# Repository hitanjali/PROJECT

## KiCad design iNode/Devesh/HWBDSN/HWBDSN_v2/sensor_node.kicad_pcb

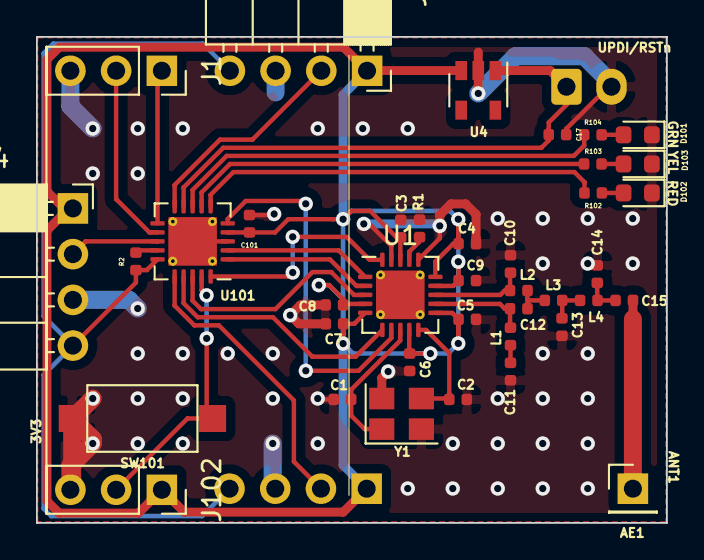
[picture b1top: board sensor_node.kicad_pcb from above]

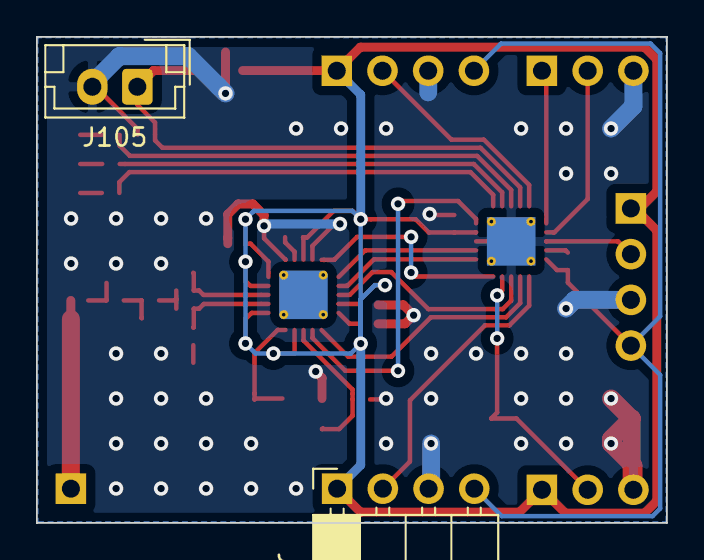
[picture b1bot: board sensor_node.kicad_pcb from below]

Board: 2 copper layers, 35.0 x 27.0 mm, 41 parts (2 on the bottom side), 33 nets.

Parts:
AE1: Antenna; PinHeader_1x01_P2.54mm_Vertical
C1: 12pF; C_0402_1005Metric
C2: 15pF; C_0402_1005Metric
C3, C4, C5, C6, C7, C8, C9: 0.1uF; C_0402_1005Metric
C10, C12: 3.9pF; C_0402_1005Metric
C11, C15: 220pF; C_0402_1005Metric
C13: 8.2pF; C_0402_1005Metric
C14: 5.6pF; C_0402_1005Metric
C17, C101: 0.1uF, 10V; C_0402_1005Metric
D101: RED; LED_0603_1608Metric
D102: YELLOW; LED_0603_1608Metric
D103: GREEN; LED_0603_1608Metric
J1: Conn_01x03_[UART]; PinSocket_1x03_P2.54mm_Vertical
J2: Conn_01x03_[PIR_1]; PinSocket_1x04_P2.54mm_Horizontal
J3: Conn_01x03_[PIR_2]; PinSocket_1x04_P2.54mm_Horizontal
J4: Conn_01x03_[PIR_3]; PinSocket_1x04_P2.54mm_Horizontal
J102: Conn_01x03_[UPDI]; PinSocket_1x03_P2.54mm_Vertical
J105: extenal_battery; JST_EH_B2B-EH-A_1x02_P2.50mm_Vertical
L1, L2, L4: 27nH; L_0402_1005Metric
L3: 22nH; L_0402_1005Metric
R1: 56K; R_0402_1005Metric
R2: 20k; R_0402_1005Metric
R102, R103, R104: 2.2K; R_0402_1005Metric
SW101: SW_Push; SW_SPST_CK_RS282G05A3
U1: CC110L; QFN-20-1EP_4x4mm_P0.5mm_EP2.7x2.7mm_ThermalVias
U4: AP7351D-30WS-7; SOT-23-5
U101: ATtiny1606-M; QFN-20-1EP_4x4mm_P0.5mm_EP2.7x2.7mm_ThermalVias
Y1: 26MHz Crystal, 10pF; Crystal_SMD_3225-4Pin_3.2x2.5mm

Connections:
+3V3: C3.1, C4.1, C5.1, C6.1, C7.1, C8.1, C9.1, C101.1, J2.1, J3.1, J4.1, J102.1, U1.4, U1.5, U1.9, U1.11, U1.14, U1.15, U1.18, U4.3, U101.4
/Sheet5FFE69EF/LDR: J2.4, J3.4, J4.4, R2.1, U101.15
/Sheet5FFE69EF/PIR_1: J2.2, U101.10
/Sheet5FFE69EF/PIR_2: J3.2, U101.16
/Sheet5FFE69EF/PIR_3: J4.2, U101.13
/Sheet5FFE69EF/to_LDR: R2.2, U101.14
/Sheet6001F810/GDO0: U1.6, U101.17
/Sheet6001F810/GDO2: U1.3, U101.18
/Sheet6001F810/GREEN: R104.1, U101.8
/Sheet6001F810/MISO: U1.2, U101.1
/Sheet6001F810/MOSI: U1.20, U101.20
/Sheet6001F810/PWR_MONITOR: C17.1, J105.1, U4.1, U101.9
/Sheet6001F810/RED: R102.1, U101.6
/Sheet6001F810/RESETn_UPDI: J102.2, SW101.1, U101.19
/Sheet6001F810/RXD: J1.1, U101.11
/Sheet6001F810/SCK: U1.1, U101.2
/Sheet6001F810/TXD: J1.2, U101.12
/Sheet6001F810/YELLOW: R103.1, U101.7
/Sheet6001F837/CSn: U1.7, U101.5
/Sheet6001F837/Q1: C1.1, U1.8, Y1.1
/Sheet6001F837/Q2: C2.1, U1.10, Y1.3
/Sheet6001F837/RFN: C10.2, L2.1, U1.13
/Sheet6001F837/RFP: C12.2, L1.2, U1.12
GND: C1.2, C2.2, C3.2, C4.2, C5.2, C6.2, C7.2, C8.2, C9.2, C10.1, C11.2, C13.2, C14.1, C17.2, C101.2, D101.1, D102.1, D103.1, J1.3, J2.3, J3.3, J4.3, J102.3, J105.2, R1.1, SW101.2, U1.16, U1.19, U4.2, U101.3, U101.21, Y1.2, Y1.4
unnamed: AE1.1, C15.2
unnamed: C11.1, L1.1
unnamed: C12.1, L2.2, L3.2
unnamed: C13.1, L3.1, L4.2
unnamed: C14.2, C15.1, L4.1
unnamed: D101.2, R102.2
unnamed: D102.2, R103.2
unnamed: D103.2, R104.2
unnamed: R1.2, U1.17

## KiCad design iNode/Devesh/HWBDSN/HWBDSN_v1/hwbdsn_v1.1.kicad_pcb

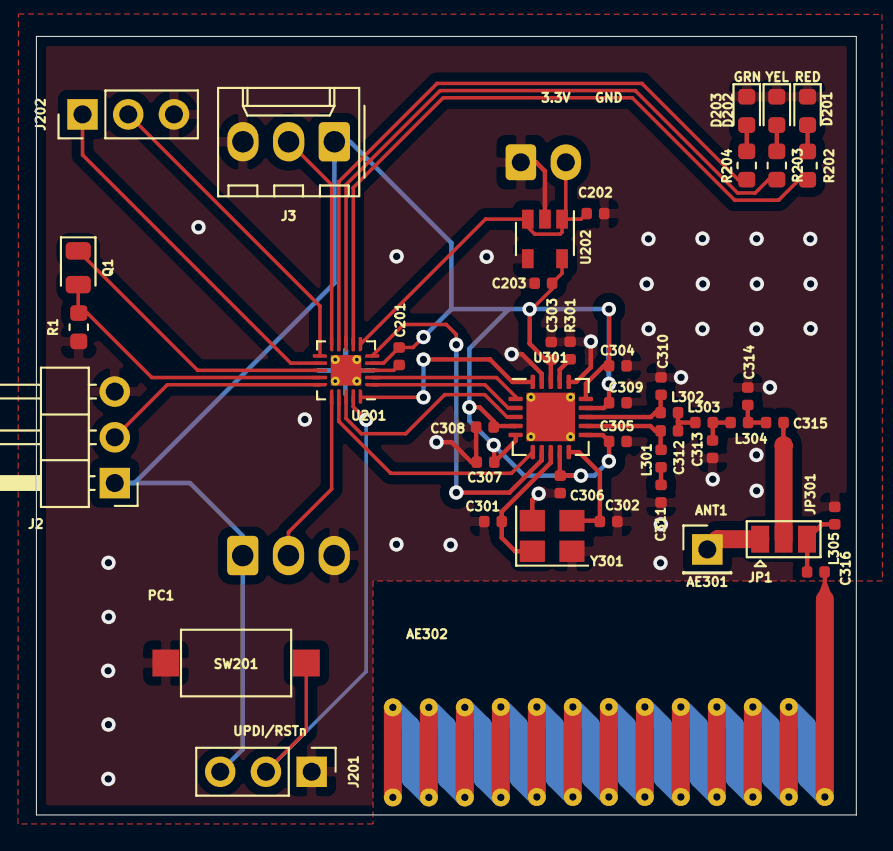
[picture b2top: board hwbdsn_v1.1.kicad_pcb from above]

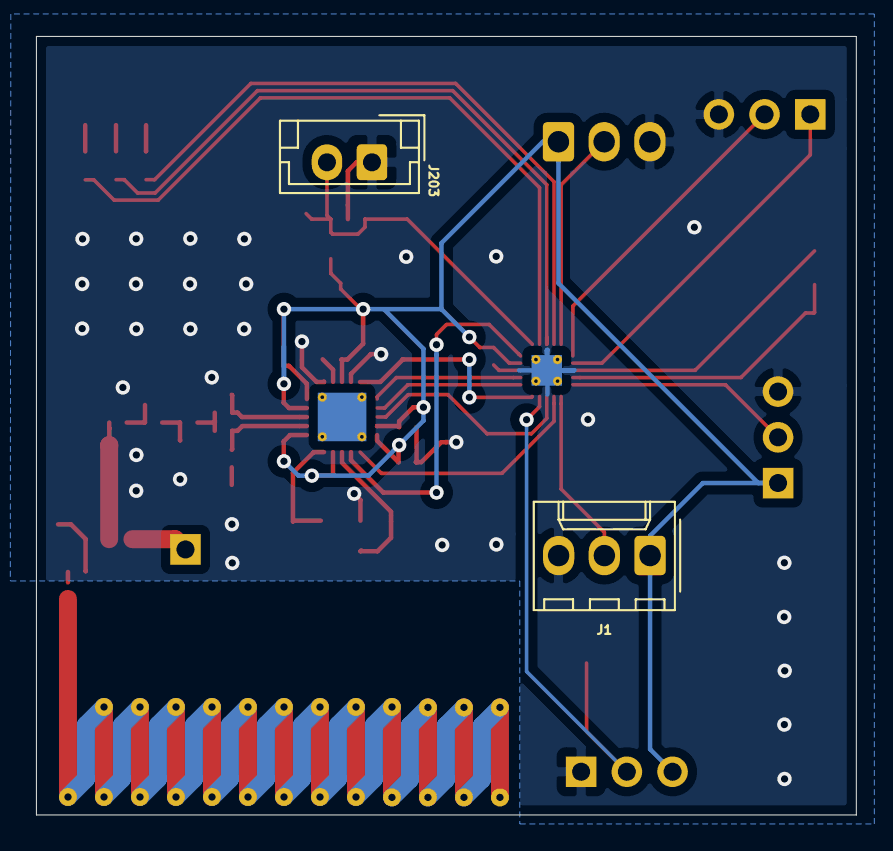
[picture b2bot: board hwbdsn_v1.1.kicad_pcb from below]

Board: 2 copper layers, 45.6 x 43.2 mm, 47 parts (2 on the bottom side), 36 nets.

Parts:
AE301: Antenna; PinHeader_1x01_P2.54mm_Vertical
AE302: Antenna; 433MhZ_basedOn_Texas_SWRA416_868MHz_915MHz
C201, C202, C203: 0.1uF, 10V; C_0402_1005Metric
C301: 12pF; C_0402_1005Metric
C302: 15pF; C_0402_1005Metric
C303, C304, C305, C306, C307, C308, C309: 0.1uF; C_0402_1005Metric
C310, C312: 3.9pF; C_0402_1005Metric
C311, C315: 220pF; C_0402_1005Metric
C313: 8.2pF; C_0402_1005Metric
C314: 5.6pF; C_0402_1005Metric
C316: 0.9 pF; C_0402_1005Metric
D201: LED_RED; LED_0603_1608Metric
D202: LED_YELLOW; LED_0603_1608Metric
D203: LED_GREEN; LED_0603_1608Metric
J1, J3: 171856-0003; Molex_KK-254_AE-6410-03A_1x03_P2.54mm_Vertical
J2: 171857-0003; PinHeader_1x03_P2.54mm_Horizontal
J201, J202: Conn_01x03; PinHeader_1x03_P2.54mm_Vertical
J203: Conn_01x02; JST_EH_B2B-EH-A_1x02_P2.50mm_Vertical
JP301: Jumper_3_Open; SolderJumper-3_P1.3mm_Open_Pad1.0x1.5mm
L301, L302, L304: 27nH; L_0402_1005Metric
L303: 22nH; L_0402_1005Metric
L305: 56nH; L_0402_1005Metric
Q1: SFH_3711; LED_0805_2012Metric
R1: 2.7K; R_0603_1608Metric
R202, R203, R204: 2.2K; R_0603_1608Metric
R301: 56K; R_0402_1005Metric
SW201: SW_Push; SW_SPST_CK_RS282G05A3
U201: ATtiny1606-M; VQFN-20-1EP_3x3mm_P0.4mm_EP1.7x1.7mm_ThermalVias
U202: AP7351D-30W5-7; SOT-23-5
U301: CC110L; QFN-20-1EP_4x4mm_P0.5mm_EP2.7x2.7mm_ThermalVias
Y301: 26MHz Crystal, 10pF; Crystal_SMD_3225-4Pin_3.2x2.5mm

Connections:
+3V0: C201.1, C203.1, C303.1, C304.1, C305.1, C306.1, C307.1, C308.1, C309.1, J1.1, J2.1, J3.1, J201.3, U201.4, U202.5, U301.4, U301.5, U301.9, U301.11, U301.14, U301.15, U301.18
/ATTINY1606/ALS: Q1.2, R1.2, U201.14
/ATTINY1606/CSn: U201.5, U301.7
/ATTINY1606/GDO0: U201.17, U301.6
/ATTINY1606/GDO2: U201.18, U301.3
/ATTINY1606/GREEN: R204.1, U201.9
/ATTINY1606/MISO: U201.1, U301.2
/ATTINY1606/MOSI: U201.20, U301.20
/ATTINY1606/PIR_1: J1.2, U201.16
/ATTINY1606/PIR_2: J2.2, U201.15
/ATTINY1606/PIR_3: J3.2, U201.10
/ATTINY1606/PWR_MONITOR: C202.1, J203.2, U201.6, U202.1, U202.3
/ATTINY1606/RED: R202.1, U201.7
/ATTINY1606/RESETn_UPDI: J201.2, SW201.1, U201.19
/ATTINY1606/RXD: J202.2, U201.11
/ATTINY1606/SCK: U201.2, U301.1
/ATTINY1606/TO_PHOTOTRANS: Q1.1, U201.13
/ATTINY1606/TXD: J202.1, U201.12
/ATTINY1606/YELLOW: R203.1, U201.8
/CC110L/Q1: C301.1, U301.8, Y301.1
/CC110L/Q2: C302.1, U301.10, Y301.3
/CC110L/RFN: C310.2, L302.1, U301.13
/CC110L/RFP: C312.2, L301.2, U301.12
GND: C201.2, C202.2, C203.2, C301.2, C302.2, C303.2, C304.2, C305.2, C306.2, C307.2, C308.2, C309.2, C310.1, C311.2, C313.2, C314.1, D201.1, D202.1, D203.1, J1.3, J2.3, J3.3, J201.1, J202.3, J203.1, L305.2, R1.1, R301.1, SW201.2, U201.3, U201.21, U202.2, U202.4, U301.16, U301.19, Y301.2, Y301.4
unnamed: AE301.1, JP301.1
unnamed: AE302.1, C316.1
unnamed: C311.1, L301.1
unnamed: C312.1, L302.2, L303.2
unnamed: C313.1, L303.1, L304.2
unnamed: C314.2, C315.1, L304.1
unnamed: C315.2, JP301.2
unnamed: C316.2, JP301.3, L305.1
unnamed: D201.2, R202.2
unnamed: D202.2, R203.2
unnamed: D203.2, R204.2
unnamed: R301.2, U301.17

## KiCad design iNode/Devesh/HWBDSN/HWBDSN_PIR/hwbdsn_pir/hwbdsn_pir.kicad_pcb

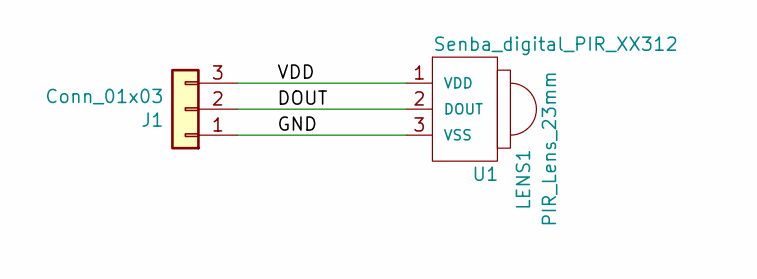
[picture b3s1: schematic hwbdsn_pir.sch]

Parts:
J1: Conn_01x03; PinHeader_1x03_P2.54mm_Vertical
LENS1: PIR_Lens_23mm; FRESNEL_LENS_S9006
U1: Senba_digital_PIR_XX312; Senba_Digital_PIR_XX312

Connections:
/DOUT: J1.2, U1.2 (DOUT)
/GND: J1.1, U1.3 (VSS)
/VDD: J1.3, U1.1 (VDD)

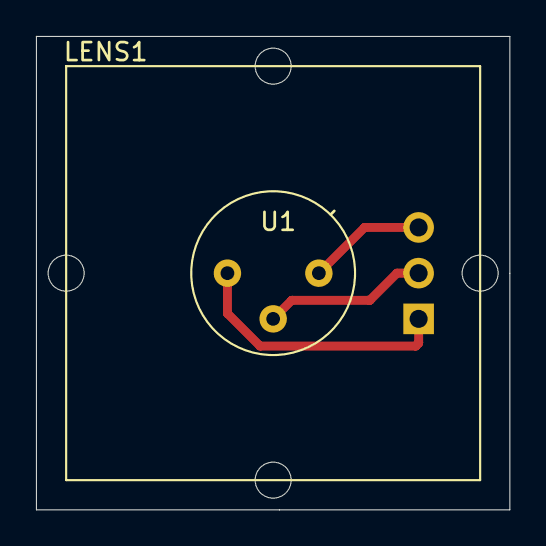
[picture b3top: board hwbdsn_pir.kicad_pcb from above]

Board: 2 copper layers, 26.3 x 26.3 mm, 3 parts (1 on the bottom side), 3 nets.

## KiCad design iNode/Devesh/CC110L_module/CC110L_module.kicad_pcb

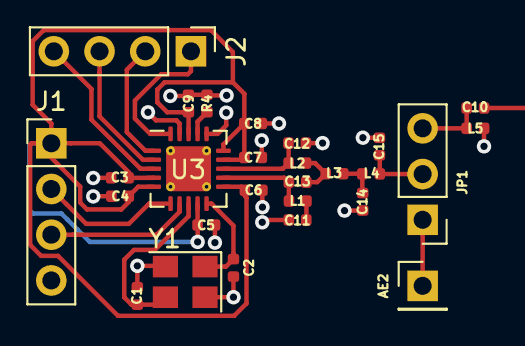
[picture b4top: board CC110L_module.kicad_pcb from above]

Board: 2 copper layers, 27 parts (0 on the bottom side), 19 nets.

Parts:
AE2: Antenna; PinHeader_1x01_P2.54mm_Vertical
C1: 22uF; C_0402_1005Metric
C2: 27uF; C_0402_1005Metric
C3, C4, C5, C6, C7, C8, C9: 0.1uF; C_0402_1005Metric
C10: 0.9 pF; C_0402_1005Metric
C11: 220pF; C_0402_1005Metric
C12, C13: 3.9pF; C_0402_1005Metric
C14: 8.2pF; C_0402_1005Metric
C15: 56pF; C_0402_1005Metric
J1, J2: Conn_01x04; PinHeader_1x04_P2.54mm_Vertical
JP1: Jumper_3_Open; PinHeader_1x03_P2.54mm_Vertical
L1, L2, L4: 0.027uH; L_0402_1005Metric
L3: 0.022uH; L_0402_1005Metric
L5: 0.56uH; L_0402_1005Metric
R4: 56K; R_0402_1005Metric
U3: CC110L; QFN-20-1EP_4x4mm_P0.5mm_EP2.5x2.5mm_ThermalVias
Y1: 26MHz; Crystal_SMD_3225-4Pin_3.2x2.5mm

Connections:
+3V3: C3.1, C4.1, C5.1, C6.1, C7.1, C8.1, C9.1, J1.1, U3.4, U3.5, U3.9, U3.11, U3.14, U3.15, U3.18
/CSn: J1.3, U3.7
/GDO0: J1.2, U3.6
/GDO2: J2.4, U3.3
/MISO: J2.3, U3.2
/MOSI: J2.1, U3.20
/Q1: C1.1, U3.8, Y1.3
/Q2: C2.1, U3.10, Y1.1
/RF1: C13.2, L1.2, U3.12
/RF2: C12.2, L2.1, U3.13
/SCLK: J2.2, U3.1
GND: C1.2, C2.2, C3.2, C4.2, C5.2, C6.2, C7.2, C8.2, C9.2, C11.2, C12.1, C14.2, C15.2, J1.4, L5.2, R4.2, U3.16, U3.19, Y1.2, Y1.4
unnamed: AE2.1, JP1.1
unnamed: C10.2, JP1.3, L5.1
unnamed: C11.1, L1.1
unnamed: C13.1, L2.2, L3.1
unnamed: C14.1, L3.2, L4.1
unnamed: C15.1, JP1.2, L4.2
unnamed: R4.1, U3.17

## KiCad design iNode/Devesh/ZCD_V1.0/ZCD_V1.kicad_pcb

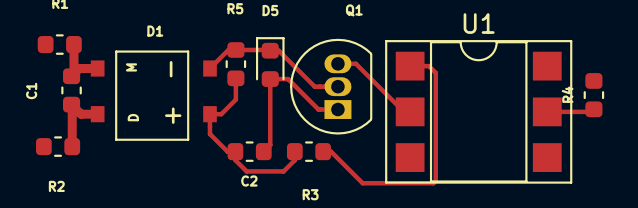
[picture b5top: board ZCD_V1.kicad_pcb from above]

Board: 2 copper layers, 11 parts (0 on the bottom side), 9 nets.

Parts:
C1: 1nF; C_0603_1608Metric
C2: 10uF/10v; C_0603_1608Metric
D1: MDS 5; MDS_5_diode_bridge
D5: 1N4148X-TP; D_0603_1608Metric
Q1: 2N3904; TO-92_Inline
R1, R2: 220k; R_0603_1608Metric
R3: 1k; R_0603_1608Metric
R4: 4.7k; R_0603_1608Metric
R5: 22k; R_0603_1608Metric
U1: 4N35; DIP-6_W7.62mm_SMDSocket_SmallPads

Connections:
AC: R1.2, R2.2
unnamed: C1.1, D1.3, R1.1
unnamed: C1.2, D1.4, R2.1
unnamed: C2.1, D1.1, R3.2, R5.1
unnamed: C2.2, D5.2, Q1.1
unnamed: D1.2, D5.1, Q1.2, R5.2
unnamed: Q1.3, U1.2
unnamed: R3.1, U1.1
OUT: R4.1, U1.5

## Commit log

2020-03-11 Documents
2020-03-11 Removed unwatned files
2020-03-11 Remove unwated files
2020-03-11 Short pdf
2020-03-18 Added firebase code and separated MQTT
2020-04-16 EEPROM changes for the SSID PASS and the mesh
2020-04-17 ESP8266 initial mesh cred update and other files
2020-04-21 COnfigurable leaf and root nodes
2020-04-22 Power ON state as per the last state
2020-04-22 Added device control on root node and last state
2020-04-24 Common root and leaf node code
2020-04-27 MQTT based cred updates
2020-04-30 Router re-connection issue MQTT reconnect solved
2020-05-04 TCP link break and re connect
2020-05-04 Changes in the verions history
2020-05-06 task exp and common root mqtt tasks changes
2020-05-11 ClientId min lenght requirement
2020-05-14 Root node reconnection issue
2020-05-28 Dimmer inteerupt based
2020-05-28 Adding the dimmer logic
2020-06-03 Dimmer code added
2020-06-04 Arduino read for the dimmer
2020-06-05 Dimmer with arduino over interrupts
2020-06-05 New changes started for muxed device and topics
2020-06-05 Dimmer observations txt file
2020-06-05 code clean up
2020-06-06 Select logic , erase implementation , not compilable
2020-06-08 4 Dimmer/ 16 device support. Topic mgmt pedning. May not compile
2020-06-10 Compile : True , Testing : Pending
2020-06-10 Changed the IO pins as DOUT same as BUILTIN indicator
2020-06-11 Dimmer last state stored in Arduino + absolute vale communication
2020-06-12 Bug fir dimmer ch 0,2,3 fixed made as 1
2020-06-12 Slowness multiplier added
2020-06-25 Initial Flicker issue with reset and powercycle + bulb off logic
2020-08-07 New project
2020-08-07 ZCD folder added
2020-08-07 Remane files
2020-09-10 Rename ZCD v-1.pro to ZCD_V1.pro
2020-09-10 Rename ZCD v-1.sch to ZCD_V1.sch
2020-09-22 Create SENSOR_MODULE
2020-10-12 Create nrf52833
2020-10-12 Create txt
2020-10-30 Create text
2020-12-18 Parking config scheme and flow
2020-12-18 Changes to allign all the lables
2020-12-21 Heartbeat scheme added
2020-12-21 Heartbeat changes
2021-01-13 Create read me
2021-01-29 Documents related to schemes etc
2021-02-01 Photo Trans experiment observation
2021-03-15 Config scheme UNIQUE address based address scheme
2021-03-19 PIR sensor schematic
